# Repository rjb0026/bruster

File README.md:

# Brucester Guitar Pedal

Kicad project for a boost guitar pedal. Based on [this schematic](https://www.diystompboxes.com/pedals/booster25.JPG). Original design by Jack Orman.

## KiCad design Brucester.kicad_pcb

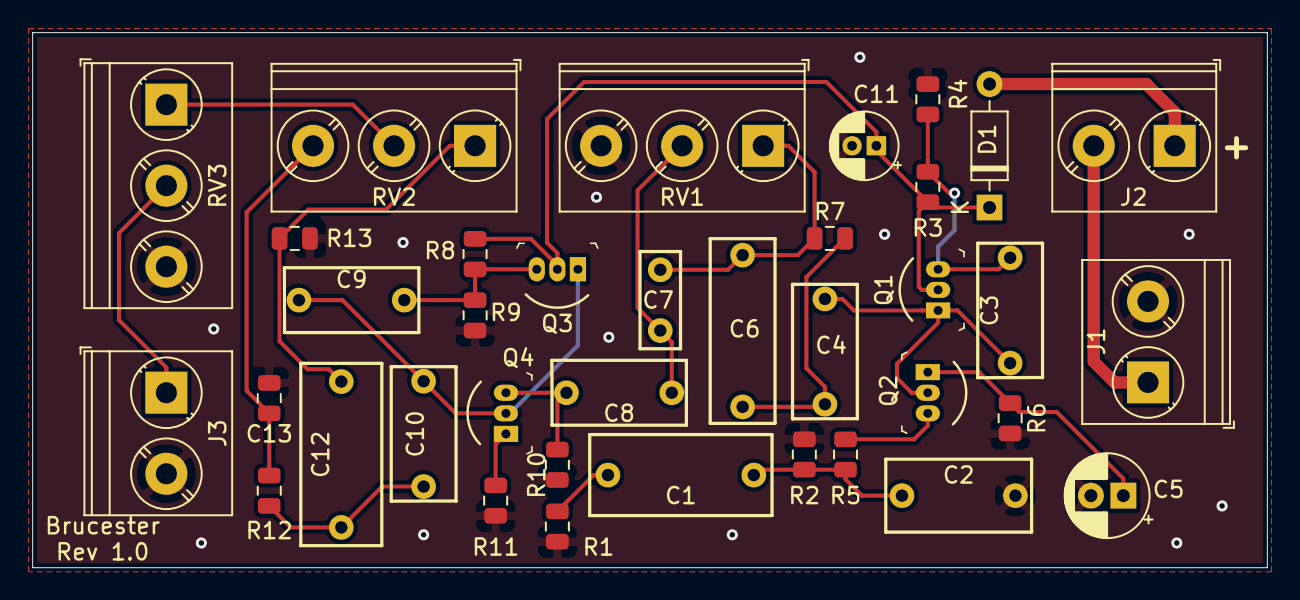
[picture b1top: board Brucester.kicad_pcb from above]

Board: 2 copper layers, 76.2 x 33.0 mm, 37 parts (0 on the bottom side), 22 nets.

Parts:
C1, C12: 0.01uF; C_Rect_L11.25mm_W5.0mm_P9.0mm
C2: 24pF; C_Rect_L9.0mm_W4.5mm_P7.0mm
C3, C4, C8, C9, C10: 0.1uF; C_Rect_L8.3mm_W4.0mm_P6.5mm
C5: 22uF; CP_Radial_D5.0mm_P2.00mm
C6: 470pF; C_Rect_L10.75mm_W4.0mm_P9.25mm
C7: 0.001uF; C_Rect_L4.0mm_W2.5mm_P3.75mm
C11: 10uF; CP_Radial_D4.0mm_P1.50mm
C13: 0.022uF; C_0805_2012Metric
D1: 1N4148; D_DO-35_SOD27_P7.62mm_Horizontal
J1: Stereo Jack Input; TerminalBlock_Phoenix_PT-1,5-2-5.0-H_1x02_P5.00mm_Horizontal
J2: Power Input; TerminalBlock_Phoenix_PT-1,5-2-5.0-H_1x02_P5.00mm_Horizontal
J3: Circuit Output; TerminalBlock_Phoenix_PT-1,5-2-5.0-H_1x02_P5.00mm_Horizontal
Q1, Q2, Q3, Q4: 2N5457_NonStock; TO-92-3
R1, R2, R3, R4, R8, R9, R10: 1M; R_0805_2012Metric
R5: 33K; R_0805_2012Metric
R6, R11: 100; R_0805_2012Metric
R7: 470K; R_0805_2012Metric
R12: 39K; R_0805_2012Metric
R13: 47K; R_0805_2012Metric
RV1: Drive 500K; TerminalBlock_Phoenix_PT-1,5-3-5.0-H_1x03_P5.00mm_Horizontal
RV2: Tone 100K-L; TerminalBlock_Phoenix_PT-1,5-3-5.0-H_1x03_P5.00mm_Horizontal
RV3: Volume 100K-A; TerminalBlock_Phoenix_PT-1,5-3-5.0-H_1x03_P5.00mm_Horizontal

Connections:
GND: C2.1, C5.2, C11.2, C13.1, J1.2, J3.2, R1.2, R2.2, R4.2, R6.2, R9.2, R10.2, R11.2, R13.1, RV1.3, RV3.3
unnamed: C1.1, C2.2, R2.1, R5.2
unnamed: C1.2, R1.1
unnamed: C3.1, C4.2, Q1.1, Q2.2
unnamed: C3.2, Q1.3, R3.2, R4.1
unnamed: C4.1, C6.1, R7.2
unnamed: C5.1, Q2.1, R6.1
unnamed: C6.2, C7.2, R7.1, RV1.1
unnamed: C7.1, C8.2, RV1.2
unnamed: C8.1, Q4.3, R10.1
unnamed: C9.2, Q3.3, R8.2, R9.1
unnamed: C10.1, C12.2, R12.1
unnamed: C9.1, C10.2, Q3.1, Q4.2
unnamed: C11.1, D1.1, Q1.2, Q3.2, R3.1, R8.1
unnamed: C12.1, R13.2, RV2.1
unnamed: C13.2, R12.2, RV2.3
unnamed: D1.2, J2.1
unnamed: J1.1, J2.2
unnamed: J3.1, RV3.2
unnamed: Q2.3, R5.1
unnamed: Q4.1, R11.1
unnamed: RV2.2, RV3.1

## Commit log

2019-07-28 Initial commit.
